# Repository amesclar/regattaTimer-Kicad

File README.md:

# sailingRegattaTimer
<!-- TOC depthFrom:1 depthTo:6 withLinks:1 updateOnSave:1 orderedList:0 -->

- [sailingRegattaTimer](#sailingregattatimer)
	- [Key Features](#key-features)
	- [Completed Project](#completed-project)
	- [Sponsorship](#sponsorship)
	- [Assembly Notes](#assembly-notes)
	- [Connector Wiring](#connector-wiring)
	- [Images](#images)
	- [Terminal Block Configuration](#terminal-block-configuration)
	- [Photos](#photos)
	- [Parts list](#parts-list)
	- [Tools](#tools)
	- [KiCad notes](#kicad-notes)
	- [Arduino IDE 2.x - Ubuntu Install Notes](#arduino-ide-2x-ubuntu-install-notes)

<!-- /TOC -->
## Key Features
+ on/off button to save battery
+ buzzer button for direct connection
+ timer buttons for; 1 minute, 2 minute, 3 minute and 5 minute durations
+ pc board buttons and buzzer for testing

## Completed Project
| Buttons | Buzzer | Wiring |
| - | - | - |
| | | |

## Sponsorship
+ Big shout out to PCB Way for their support on this project.
+ Customer support is great; I needed to halt production due to an incomplete design (my mistake).
+ Turn-around time from design submittal to pc board delivery was less than one week for US West coast delivery.
+ See [KiCad notes](#kicad-notes) for PCB Way plug-in installation, makes ordering PC board "one button push"

+ [PCB Way - PC Board Fabricator](https://www.pcbway.com/orderonline.aspx)

## Assembly Notes
| Area | Description |
| --- | --- |
| LED | note polarity alignment |
| PC board switch |  note orientation, may have normally closed/open side |
| pins - PC board to Arduino | dry assemble then solder to ensure alignment |
| box on/off switch | 2.5" from left side, 1.5" down |
| box buttons / lights | 4" from left edge, 1.5" down, 1.5" center spacing |

## Connector Wiring
Female 2 wire to male 8 wire
| Black | Red | Male 1 - Timers | Male 2 - Other |
| - | - | - | - |
| Black | Red | 5 Min | 5v Light |
| White | Yellow | 3 Min | Reset |
| Orange | Green | 2 Min | 12v In |
| Blue | Purple | 1 Min | Not Used |

## Images
| Breadboard | Schematic | PC Board | KiCad 3D Image |
| - | - | - | - |
| | | |  |

## Terminal Block Configuration

## Photos
| PC Board (PCB Way)| PC Board with Parts | |
| - | - | - |
|  |  | |

| ProtoBoard 0 | ProtoBoard 1 | ProtoBoard 2 |
| - | - | - |
| |  | |

| Breadboard 0 | Breadboard 1 | Breadboard 2 |
| - | - | - |
| |  | |

## Parts list
Total cost approximately $200 (will have extra parts)
|item|quantity|description|[Ref URL](reference url)|(approx USD price)|
|---|---|---|---|---|
|item|quantity|description|[Ref URL](reference url)|(approx USD price)|
|---|---|---|---|---|
|1|1|1pc Arduino UNO|[Ref URL](https://www.amazon.com/ELEGOO-Board-ATmega328P-ATMEGA16U2-Compliant/dp/B01EWOE0UU/ref=asc_df_B01EWOE0UU?mcid=3c20e862567d3232bda82cbee4dcb2bc&hvocijid=5269161885874027834-B01EWOE0UU-&hvexpln=73&tag=hyprod-20&linkCode=df0&hvadid=721245378154&hvpos=&hvnetw=g&hvrand=5269161885874027834&hvpone=&hvptwo=&hvqmt=&hvdev=c&hvdvcmdl=&hvlocint=&hvlocphy=9033367&hvtargid=pla-2281435180978&psc=1)|17|
|2|1|1pc ELEGOO Electronic Fun Kit Bundle with Breadboard Cable Resistor, Capacitor, LED, Potentiometer total 235 Items for Arduino|[Ref URL](https://www.amazon.com/EL-CK-002-Electronic-Breadboard-Capacitor-Potentiometer/dp/B01ERP6WL4/ref=sr_1_11?crid=3E78O5C0JQMRR&dib=eyJ2IjoiMSJ9.ja6Gw2iVVjmRL_IDpxrlM_1JkWDSrarS-FIfg3YUNSdtdrMMc6kGePao5WWdf3jKhm03b97dspKyRrwA1jayXAXgh3y5mL8-M7roZnTalEGMoCrpncfMciwm_rssummXmvGSr-dyP1-Cob0TWXs_iEgvk04e52HivkEMU1jA5AgiYnM6080Viw3_bRxs-CekUHPcqsP5RitK2yjWbUTWIAoNqD28DXfaBpBz6HzTmRYiqtbo39AaUO2i1jVkDBAYL_qbY1YTQppkVhUR9CSqvGZWajfBk9ogVTgigdGSB161gCnIcicyctFr47A0c2xrzIbage1vQrp3VE0vql_cmWAdDW3s2hJN9ygKd6unQIg.PKvSQYPt9dDgSAw5WOU__V5wuUMjGVD52MEJAk5rdvw&dib_tag=se&keywords=arduino+led&qid=1738088621&s=electronics&sprefix=arduino+led%2Celectronics%2C216&sr=1-11)|10|
|3|1|1pc 12V 7Ah (7.2Ah) Lithium LiFePO4 Deep Cycle Battery|[Ref URL](https://www.amazon.com/gp/product/B0B78HTRDL/ref=ppx_yo_dt_b_search_asin_title?ie=UTF8&th=1)|27|
|4|1|1pc FARBIN Car Horn 12v Loud Motorcycle Horns High/Low Supertone Truck Horn Kit Electric Train Horn for Car (White horn with wire button)|[Ref URL](https://www.amazon.com/gp/product/B08Q86VWNH/ref=ox_sc_saved_title_8?smid=A3M8B4MVOJBZCN&th=1)|24|
|5|1|2pcs HAHIYO Electronic Buzzer Alarm 12V 400Hz Beep|[Ref URL](https://www.amazon.com/gp/product/B09H7RYFQ6/ref=ppx_yo_dt_b_search_asin_title?ie=UTF8&th=1)|9|
|6|1|1pcs Round Rocker Switch, 12V Toggle Switch, Waterproof Lighted LED|[Ref URL](https://www.amazon.com/gp/product/B0D91HGCCR/ref=ppx_yo_dt_b_search_asin_title?ie=UTF8&th=1)|6|
|7|1|1pc Pololu 5V, 600mA Step-Down Voltage Regulator D36V6F5|[Ref URL](https://www.pololu.com/product/3792)|10|
|8|1|1pc 6 Pcs Mini Plastic Boxes, 5'' x 3'' x 1.8'' Small Clear Storage Containers|[Ref URL](https://www.amazon.com/gp/product/B0CLLKK5ZK/ref=ox_sc_act_title_1?smid=A1RUKIRXEA30DB&th=1)|15|
|9|1|1pc 73Pcs(6Sets) Terminal Block Set, 6Pcs 12 Positions 600V|[Ref URL](https://www.amazon.com/dp/B08GCF76K8?ref=ppx_yo2ov_dt_b_fed_asin_title&th=1)|16|
|10|1|5pcs 8mm 3V-4.5V-5V-6V-7.5V-9VDC LED Metal Indicator Light Waterproof Signal Lamp|[Ref URL](https://www.amazon.com/dp/B09L7W7HKL?ref=ppx_yo2ov_dt_b_fed_asin_title&th=1)|8|
|11|1|100Pcs Jst 2.0 Ph 2 Pin Connector Plug|[Ref URL](https://www.amazon.com/dp/B0DMW21LWS?ref=ppx_yo2ov_dt_b_fed_asin_title&th=1)|16|
|12|1|XINGYHENG 40PCS (20Pairs) 8PIN Female and Male Connecting Plug with Terminal Connector Wire Cable|[Ref URL](https://www.amazon.com/dp/B08H55TNJX?ref=ppx_yo2ov_dt_b_fed_asin_title)|12|
|13|1|WWZMDiB 840 Pin Breadboard Jumper Wires Kit|[Ref URL](https://www.amazon.com/dp/B0BWGZRGYP?ref=ppx_yo2ov_dt_b_fed_asin_title)|8|
|14|1|Twidec/12PCS 12V 250V Momentary Push Button Switch 2 Pins SPST 7mm 6 Colors|[Ref URL](https://www.amazon.com/dp/B07RTZVZ6L?ref=ppx_yo2ov_dt_b_fed_asin_title&th=1)|8|
|15|1|GRAVITY DIGITAL 5A RELAY MODULE|[Ref URL](https://www.digikey.com/en/products/detail/dfrobot/DFR0017/6588499)|10|
|16|1|BUNKER HILL SECURITY 0.50 Caliber Ammo Box|[Ref URL](https://www.harborfreight.com/050-caliber-ammo-box-57766.html)|9|

## Tools
|item|description|[Ref URL](reference url)|(approx USD price)|
|---|---|---|---|
|1|Arduino IDE|[Ref URL](https://www.arduino.cc/en/software)|0|
|2|Fritzig diagram, schematic, board layout|[Ref URL](https://fritzing.org/download/)|0|
|3|Fanttik T1 Max Soldering Iron Kit|[Ref URL](https://www.amazon.com/gp/product/B0D41ZMDPD/ref=ox_sc_saved_title_1?smid=A30MIYRTO6RN4I&psc=1)|80|
|4|IRWIN VISE-GRIP Wire Stripper|[Ref URL](https://www.amazon.com/dp/B000OQ21CA?ref=ppx_yo2ov_dt_b_fed_asin_title&th=1)|25|
|5|KOTTO Strong Suction Smoke Absorber|[Ref URL](https://www.amazon.com/dp/B07ZHH5H7N?ref=ppx_yo2ov_dt_b_fed_asin_title)|80|

## KiCad notes
+ When ordering pc board use PCB Way menu button
+ Kicad has been stable and has a large library of items with predefined footprints. It's sometimes hard to find the specific item of interest.
+ Note, I initially tried Fritzig. It was not stable and it would intermittently drop items from drawings.

| KiCad Plugin Manager | PCB Way Plugin | PCB Way Toolbar Icon | Edge.Cut Create Option | Gerber & Drill File Export |
| - | - | - | - | - |
|  |  |  |  | |  |

## Arduino IDE 2.x - Ubuntu Install Notes
>FATAL:setuid_sandbox_host.cc(158)] The SUID sandbox helper binary was found, but is not configured correctly.

From (https://askubuntu.com/questions/1515105/sandbox-problems-with-arduino-ides-with-24-04)

The issue comes from Ubuntu 24.04 deprecating unprivileged kernel namespaces, which the Arduino IDE (and other applications) rely on for their sandboxes

To solve this, you can create a new AppArmor profile for the Arduino IDE. Assuming you installed it in /home/username/bin/arduino (that's the whole filename), you can do something like sudo vim /etc/apparmor.d/home.username.bin.arduino (or nano, or some other editor) and write:
```
abi <abi/4.0>,
include <tunables/global>
profile arduino /home/username/bin/arduino flags=(unconfined) {
  userns,
  include if exists <local/arduino>
}
```
Then `run sudo service apparmor reload`

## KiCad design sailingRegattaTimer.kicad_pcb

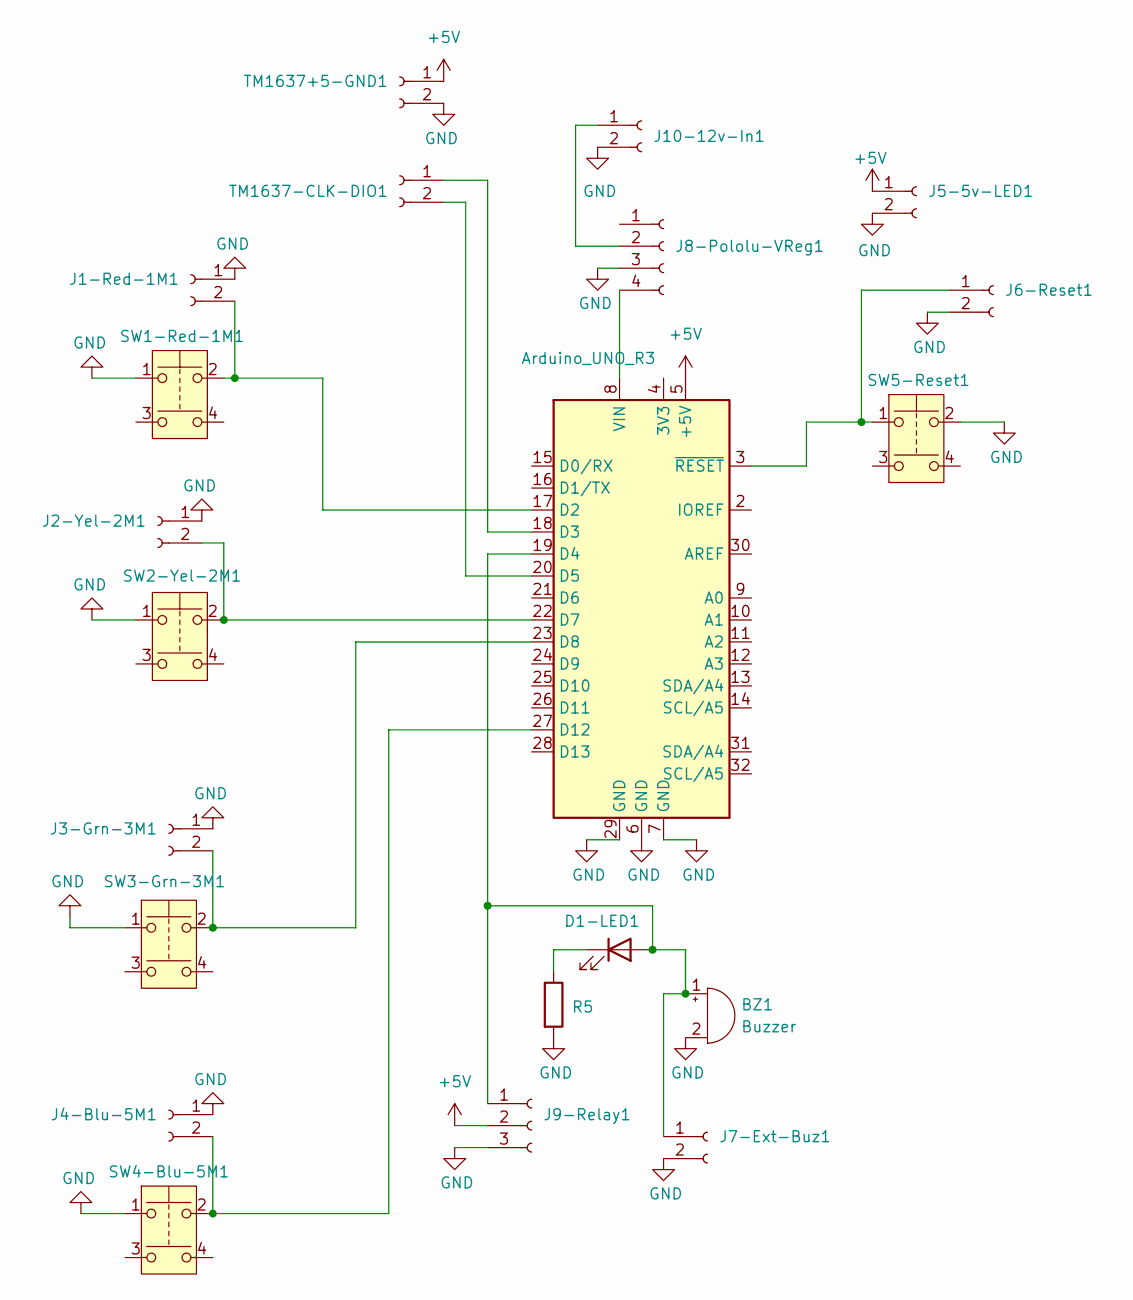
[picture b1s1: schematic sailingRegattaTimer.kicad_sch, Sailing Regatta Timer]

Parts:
A1: Arduino_UNO_R3
BZ1: Buzzer; Buzzer_12x9.5RM7.6
D1-LED1: LED; LED_D3.0mm
J1-Red-1M1, J2-Yel-2M1, J5-5v-LED1, J7-Ext-Buz1, J10-12v-In1: Conn_01x02_Socket; PinSocket_1x02_P2.54mm_Vertical
J3-Grn-3M1: J3-Grn-3M; PinSocket_1x02_P2.54mm_Vertical
J4-Blu-5M1: J4-Blu-5M1; PinSocket_1x02_P2.54mm_Vertical
J6-Reset1: J6-Reset; PinSocket_1x02_P2.54mm_Vertical
J8-Pololu-VReg1: Conn_01x04_Socket; PinSocket_1x04_P2.54mm_Vertical
J9-Relay1: Conn_01x03_Socket; PinSocket_1x03_P2.54mm_Vertical
R5: R_Axial_DIN0204_L3.6mm_D1.6mm_P1.90mm_Vertical
SW1-Red-1M1, SW2-Yel-2M1, SW3-Grn-3M1, SW4-Blu-5M1, SW5-Reset1: SW_PUSH_6mm
TM1637+5-GND1, TM1637-CLK-DIO1: Conn_01x02_Socket; PinSocket_1x02_P2.54mm_Vertical

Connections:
+5V: A1.5 (+5V), J5-5v-LED1.1, J9-Relay1.2, TM1637+5-GND1.1
GND: A1.6 (GND), A1.7 (GND), A1.29 (GND), BZ1.2 (-), J1-Red-1M1.1, J2-Yel-2M1.1, J3-Grn-3M1.1, J4-Blu-5M1.1, J5-5v-LED1.2, J6-Reset1.2, J7-Ext-Buz1.2, J8-Pololu-VReg1.3, J9-Relay1.3, J10-12v-In1.2, R5.2, SW1-Red-1M1.1, SW2-Yel-2M1.1, SW3-Grn-3M1.1, SW4-Blu-5M1.1, SW5-Reset1.2, TM1637+5-GND1.2
unnamed: A1.17 (D2), J1-Red-1M1.2, SW1-Red-1M1.2
unnamed: A1.18 (D3), TM1637-CLK-DIO1.1
unnamed: A1.19 (D4), BZ1.1 (+), D1-LED1.2 (A), J7-Ext-Buz1.1, J9-Relay1.1
unnamed: A1.20 (D5), TM1637-CLK-DIO1.2
unnamed: A1.22 (D7), J2-Yel-2M1.2, SW2-Yel-2M1.2
unnamed: A1.23 (D8), J3-Grn-3M1.2, SW3-Grn-3M1.2
unnamed: A1.27 (D12), J4-Blu-5M1.2, SW4-Blu-5M1.2
unnamed: A1.8 (VIN), J8-Pololu-VReg1.4
unnamed: A1.3 (~RESET), J6-Reset1.1, SW5-Reset1.1
unnamed: D1-LED1.1 (K), R5.1
unnamed: J8-Pololu-VReg1.2, J10-12v-In1.1

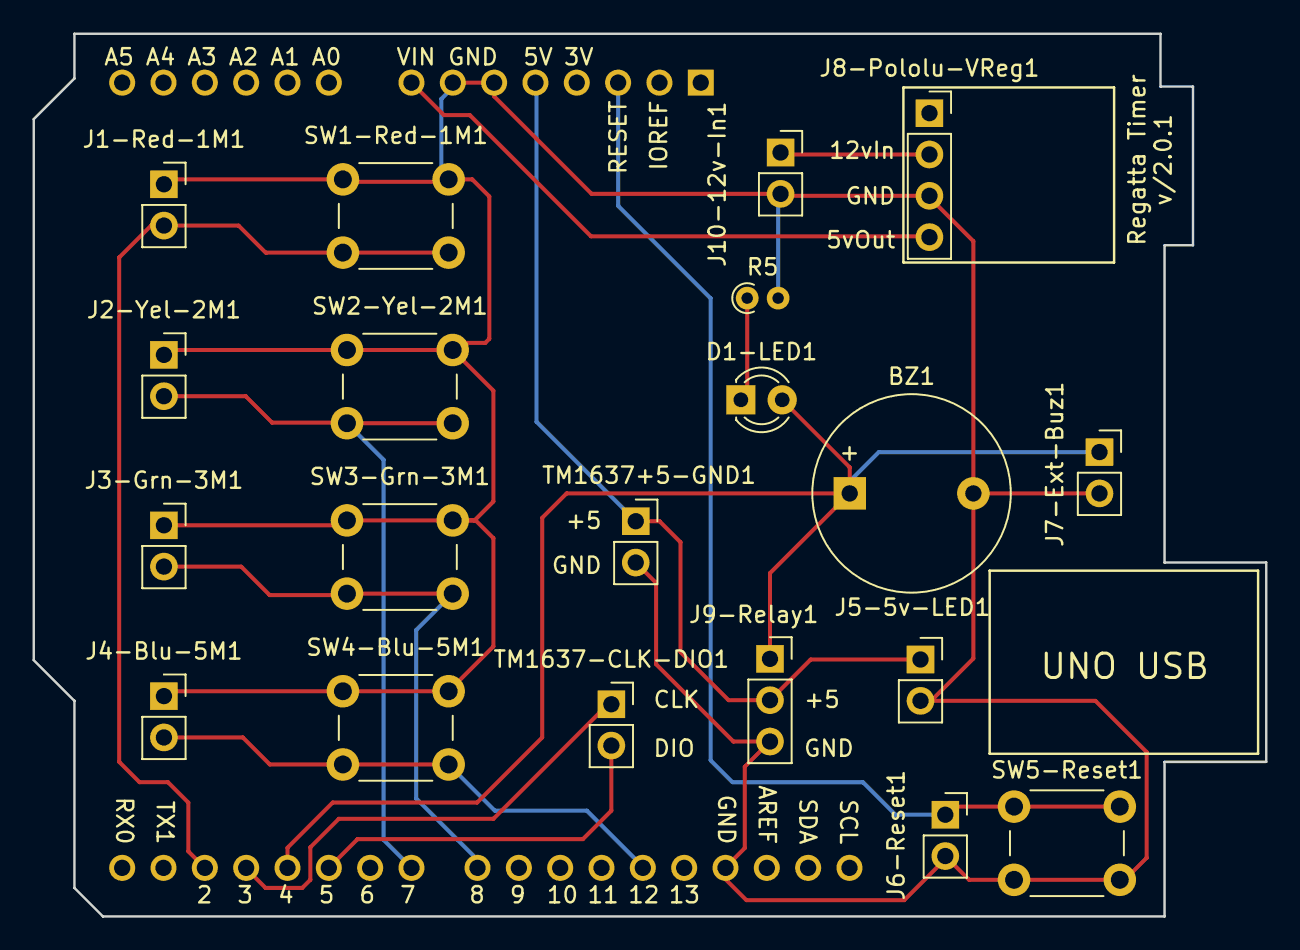
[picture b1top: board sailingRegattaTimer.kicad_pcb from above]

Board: 2 copper layers, 75.8 x 54.2 mm, 21 parts (0 on the bottom side), 13 nets.

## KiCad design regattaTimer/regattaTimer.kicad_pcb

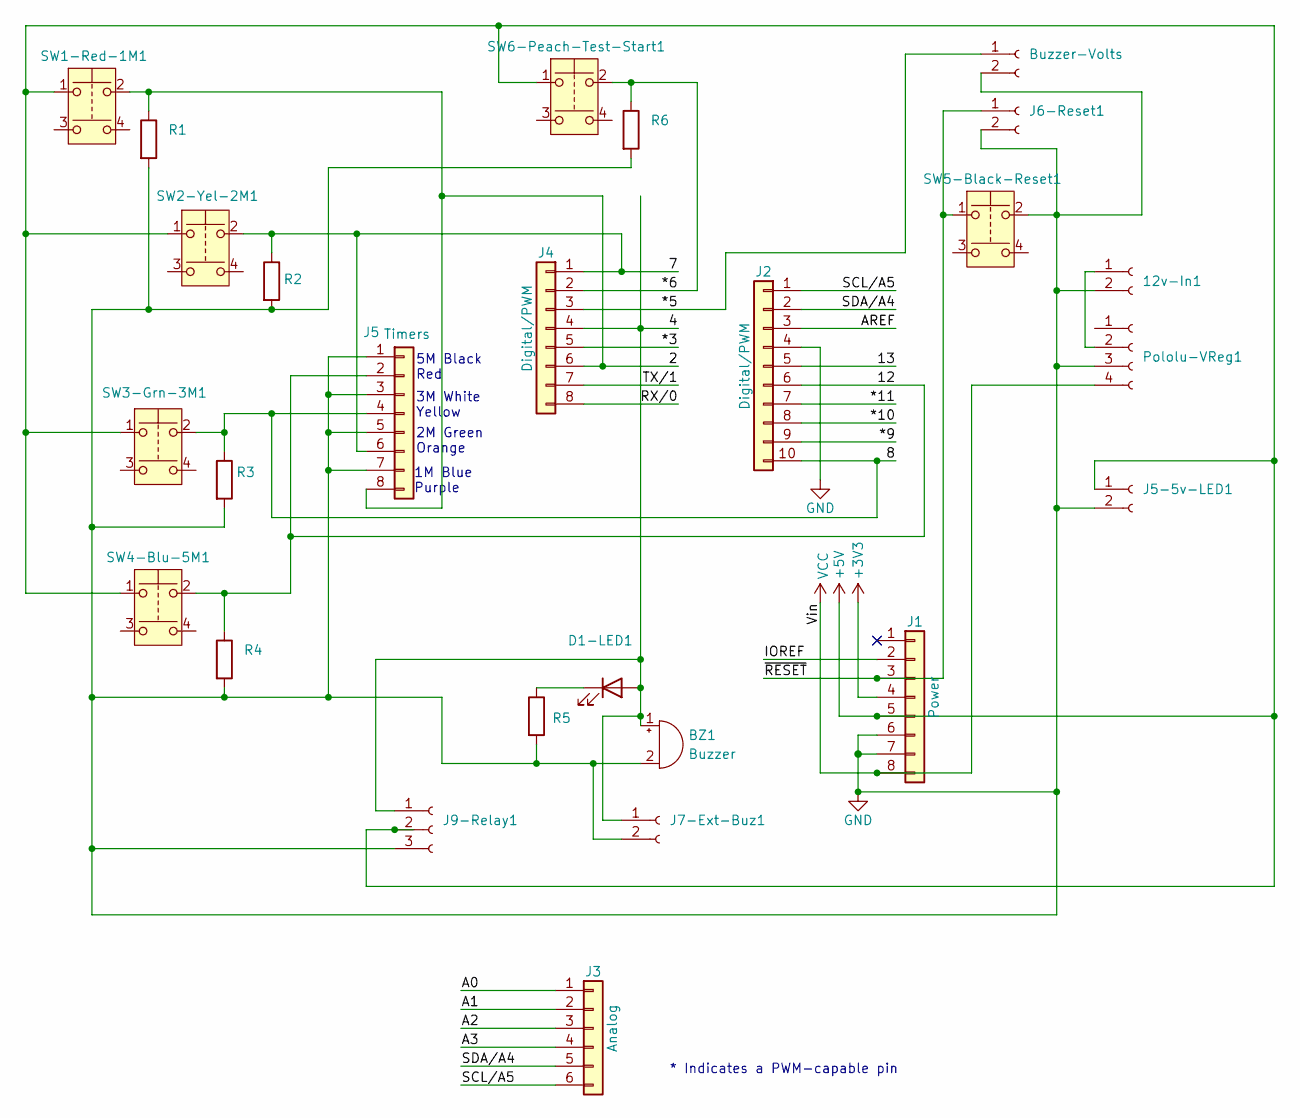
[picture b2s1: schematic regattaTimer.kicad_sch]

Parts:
12v-In1: Conn_01x02_Socket; PinSocket_1x02_P2.54mm_Vertical
BZ1: Buzzer; Buzzer_12x9.5RM7.6
Buzzer-Volts: PinSocket_1x02_P2.54mm_Vertical
D1-LED1: LED; LED_D1.8mm_W1.8mm_H2.4mm_Horizontal_O1.27mm_Z1.6mm
J1: Power; PinSocket_1x08_P2.54mm_Vertical
J2: Digital/PWM; PinSocket_1x10_P2.54mm_Vertical
J3: Analog; PinSocket_1x06_P2.54mm_Vertical
J4: Digital/PWM; PinSocket_1x08_P2.54mm_Vertical
J5: Timers; PinSocket_1x08_P2.54mm_Vertical
J5-5v-LED1, J7-Ext-Buz1: Conn_01x02_Socket; PinSocket_1x02_P2.54mm_Vertical
J6-Reset1: J6-Reset; PinSocket_1x02_P2.54mm_Vertical
J9-Relay1: Conn_01x03_Socket; PinSocket_1x03_P2.54mm_Vertical
Pololu-VReg1: Conn_01x04_Socket; PinSocket_1x04_P2.54mm_Vertical
R1, R2, R3, R4, R5, R6: R_Axial_DIN0309_L9.0mm_D3.2mm_P2.54mm_Vertical
SW1-Red-1M1, SW2-Yel-2M1, SW3-Grn-3M1, SW4-Blu-5M1, SW5-Black-Reset1, SW6-Peach-Test-Start1: SW_PUSH_6mm

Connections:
+3V3: J1.4
+5V: J1.5, J5-5v-LED1.1, J9-Relay1.2, SW1-Red-1M1.1, SW2-Yel-2M1.1, SW3-Grn-3M1.1, SW4-Blu-5M1.1, SW6-Peach-Test-Start1.1; also elsewhere on the board
/2: J4.6, J5.8, R1.1, SW1-Red-1M1.2
/4: BZ1.1 (+), D1-LED1.2 (A), J4.4, J7-Ext-Buz1.1, J9-Relay1.1
/7: J4.1, J5.6, R2.1, SW2-Yel-2M1.2
/8: J2.10, J5.4, R3.1, SW3-Grn-3M1.2
/12: J2.6, J5.2, R4.1, SW4-Blu-5M1.2
/13: J2.5
/*3: J4.5
/*5: Buzzer-Volts.1, J4.3; also elsewhere on the board
/*6: J4.2, R6.1, SW6-Peach-Test-Start1.2; also elsewhere on the board
/*9: J2.9
/*10: J2.8
/*11: J2.7
/A0: J3.1
/A1: J3.2
/A2: J3.3
/A3: J3.4
/AREF: J2.3
/IOREF: J1.2
/RX/0: J4.8
/SCL/A5: J2.1, J3.6
/SDA/A4: J2.2, J3.5
/TX/1: J4.7
/~RESET: J1.3, J6-Reset1.1, SW5-Black-Reset1.1
unnamed: D1-LED1.1 (K), R5.1
unnamed: 12v-In1.1, Pololu-VReg1.2

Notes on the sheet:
1M Blue Purple
2M Green Orange
3M White Yellow
* Indicates a PWM-capable pin
5M Black Red

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
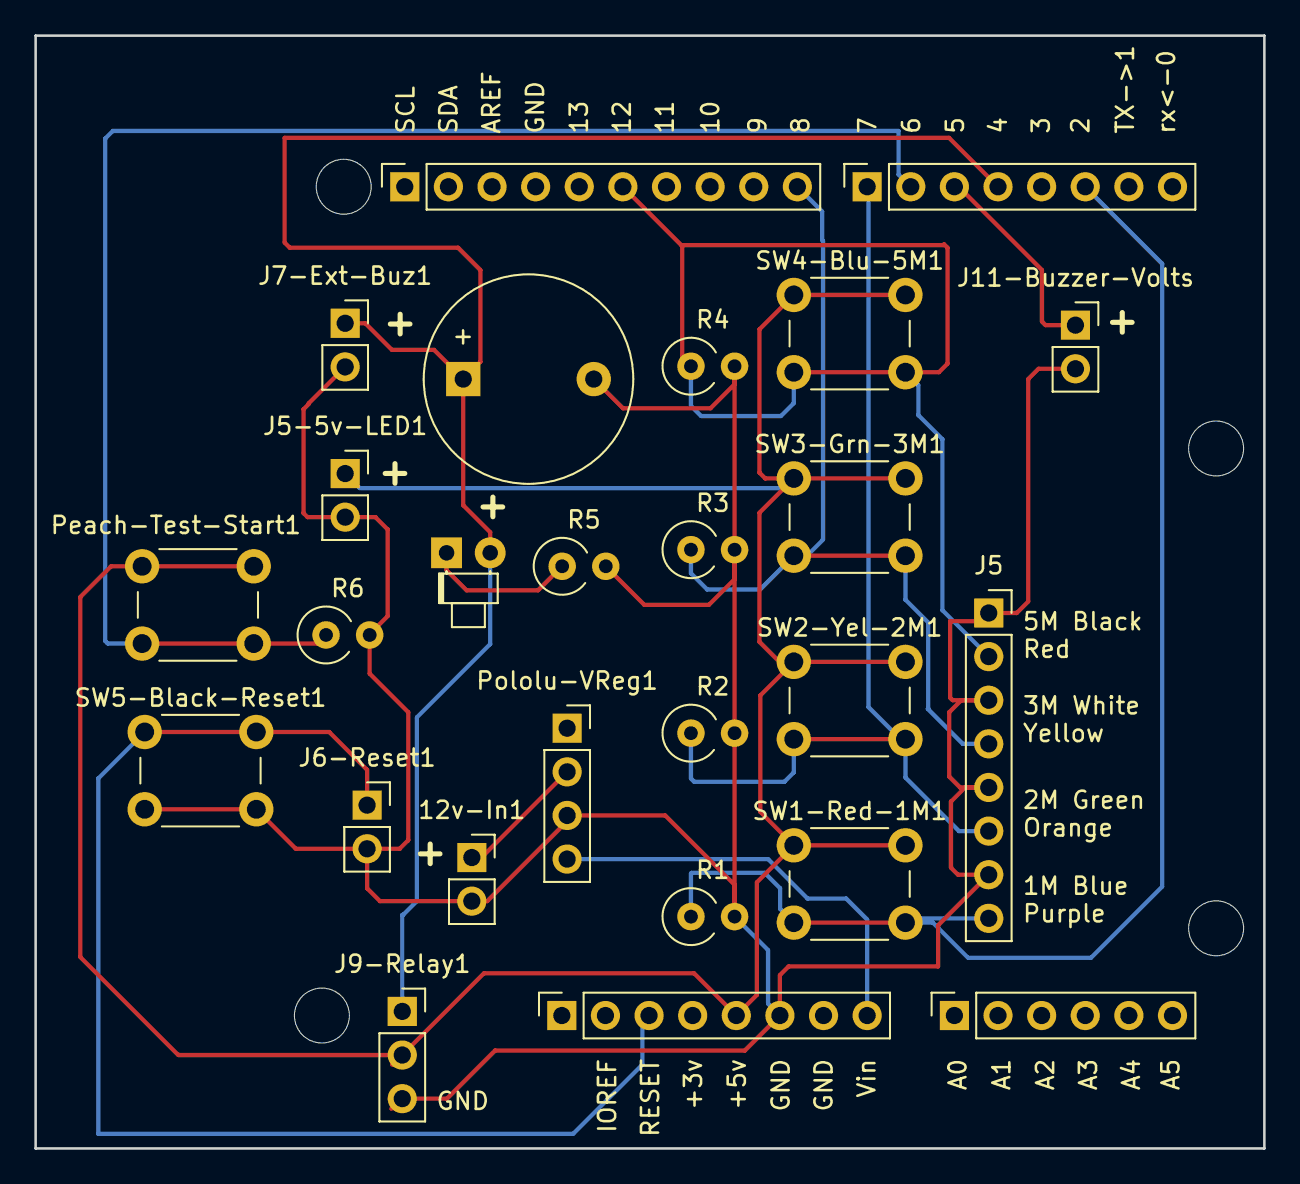
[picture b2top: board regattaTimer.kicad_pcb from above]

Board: 2 copper layers, 71.5 x 64.8 mm, 30 parts (0 on the bottom side), 14 nets.

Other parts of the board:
J11-Buzzer-Volts: J6-Reset; PinSocket_1x02_P2.54mm_Vertical
MH1, MH2, MH3, MH4: MountingHole_3.2mm
Peach-Test-Start1: SW_PUSH_6mm

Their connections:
+5V: Peach-Test-Start1.1; also elsewhere on the board
/*5: J11-Buzzer-Volts.1; also elsewhere on the board
/*6: Peach-Test-Start1.2; also elsewhere on the board

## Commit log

2025-03-14 add pc board photo and pcb way reference
2025-03-15 corrected ino file
2025-03-15 committed deleted file missed in earlier commit
2025-03-16 incremental save
2025-03-24 added production files for easier pc board ordering
2025-03-24 update files, prep for PCB Way contact
2025-03-25 commit to save interim work
2025-03-30 updated board based on physical parts layout
2025-03-31 save today's work
2025-04-03 added 12v input connector supplying voltage regulator
2025-04-04 daily checkin
2025-04-17 initial iteration completed - add xml based log messages
2025-04-23 20250423-095156 checkin based on latest board check and changes to support automated testing
2025-04-28 save current state
2025-06-18 save current working files
2025-08-24 corrected missing xml closing tag
2025-08-24 add support for 4 pin digital display - countdown timer display
2025-11-30 completed ai generated regatta timer and accompanying spec
2025-12-04 initial iteration of ai generated code completed
2025-12-05 updated spec to align with current code iteration
2025-12-06 save incremental work
2025-12-07 incremental save, updated schematic, schematic image and pcb initial
2025-12-08 incremental save updated schematic and pcb
2025-12-09 remove production files, update schematic and pcb
2025-12-10 updated images and one resistor footprint so it matched the others
2026-01-05 completed pcb flip
2026-01-05 minor update
2026-01-05 add custom uno library
2026-01-06 Revert "incremental save"
    This reverts commit 1c0ff86f2212df186ba7f97aef935cadcedda2ad.
2026-01-14 completed pcb layout
2026-02-03 initial commit - schematic and pcb
2026-03-24 partial commit to save work
2026-03-25 correct duration validation errors
2026-03-25 addressed 5min duration failure
2026-03-25 reduce drift
2026-03-26 12v in label movement
2026-03-27 add pcb annotation - uno usb
2026-03-27 add relay and other labels
2026-03-30 voltage measurement debug complete
2026-04-01 additional continuity checks
